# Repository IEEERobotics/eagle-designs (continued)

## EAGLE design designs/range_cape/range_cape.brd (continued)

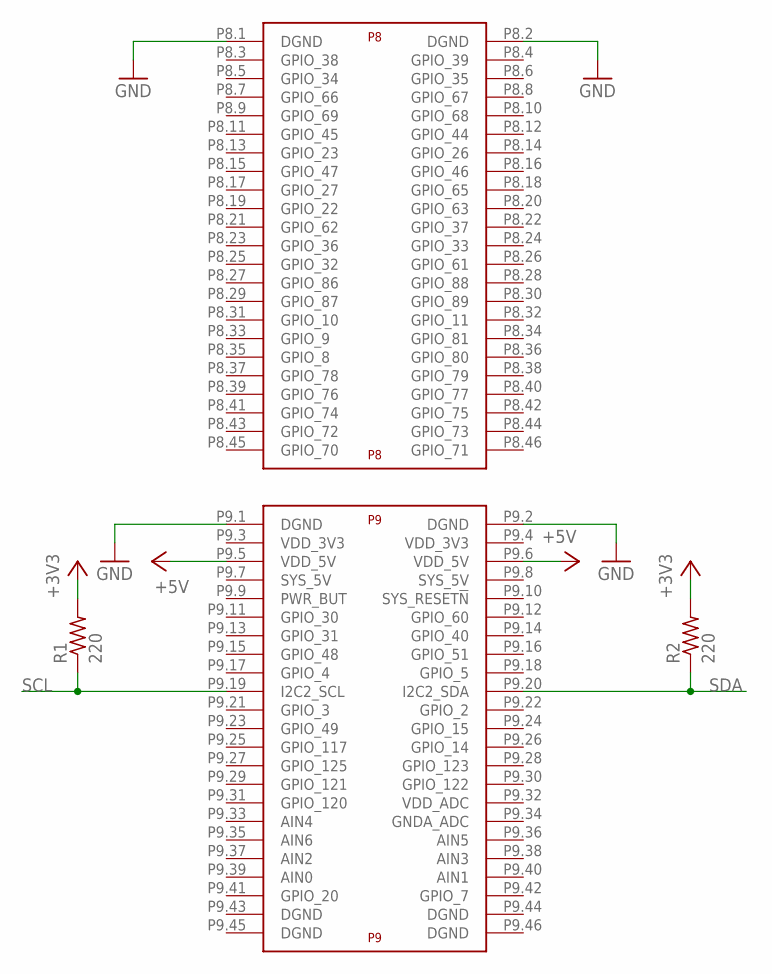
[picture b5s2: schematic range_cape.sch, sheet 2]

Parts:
R1, R2: 220; R0805W
U$1: BEAGLE_BONE_BLACK_CAPE

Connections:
+3V3: R1.2, R2.2; also elsewhere on the board
+5V: U$1.P9.5 (VDD_5V), U$1.P9.6 (VDD_5V); also elsewhere on the board
GND: U$1.P8.1 (DGND), U$1.P8.2 (DGND), U$1.P9.1 (DGND), U$1.P9.2 (DGND); also elsewhere on the board
SCL: R1.1, U$1.P9.19 (I2C2_SCL)
SDA: R2.1, U$1.P9.20 (I2C2_SDA)

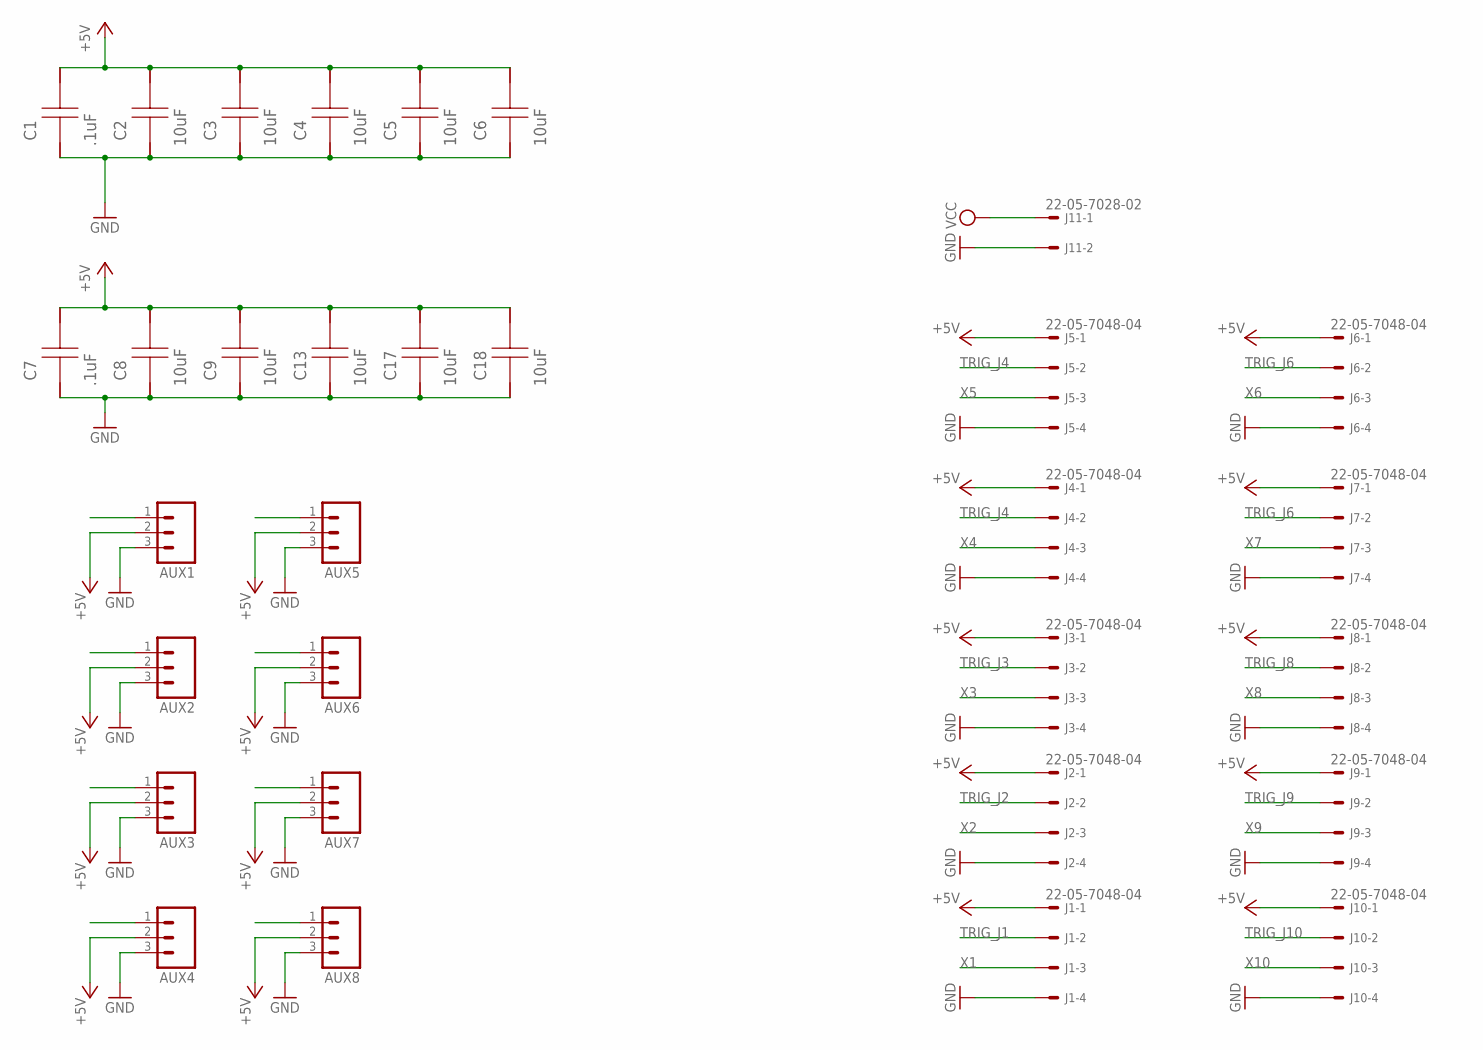
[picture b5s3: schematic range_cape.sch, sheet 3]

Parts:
AUX1, AUX2, AUX3, AUX4, AUX5, AUX6, AUX7, AUX8: M03LOCK; 1X03_LOCK
C1, C7: .1uF; 1206
C2, C3, C4, C5, C6, C8, C9, C13, C17, C18: 10uF; 1206
J1, J2, J3, J4, J5, J6, J7, J8, J9, J10: 22-05-7048-04; 7395-04
J11: 22-05-7028-02; 7395-02

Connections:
+5V: AUX1.2, AUX2.2, AUX3.2, AUX4.2, AUX5.2, AUX6.2, AUX7.2, AUX8.2, C1.1, C2.1, C3.1, C4.1, C5.1, C6.1, C7.1, C8.1, C9.1, C13.1, C17.1, C18.1, J1.1, J2.1, J3.1, J4.1, J5.1, J6.1, J7.1, J8.1, J9.1, J10.1; also elsewhere on the board
GND: AUX1.3, AUX2.3, AUX3.3, AUX4.3, AUX5.3, AUX6.3, AUX7.3, AUX8.3, C1.2, C2.2, C3.2, C4.2, C5.2, C6.2, C7.2, C8.2, C9.2, C13.2, C17.2, C18.2, J1.4, J2.4, J3.4, J4.4, J5.4, J6.4, J7.4, J8.4, J9.4, J10.4, J11.2; also elsewhere on the board
PWM_IN_1: AUX1.1; also elsewhere on the board
PWM_IN_2: AUX2.1; also elsewhere on the board
PWM_IN_3: AUX3.1; also elsewhere on the board
PWM_IN_4: AUX4.1; also elsewhere on the board
PWM_OUT_1: AUX5.1; also elsewhere on the board
PWM_OUT_2: AUX6.1; also elsewhere on the board
PWM_OUT_3: AUX7.1; also elsewhere on the board
PWM_OUT_4: AUX8.1; also elsewhere on the board
TRIG_J1: J1.2
TRIG_J2: J2.2
TRIG_J3: J3.2
TRIG_J4: J4.2, J5.2
TRIG_J6: J6.2, J7.2
TRIG_J8: J8.2
TRIG_J9: J9.2
TRIG_J10: J10.2
VCC: J11.1; also elsewhere on the board
X1: J1.3; also elsewhere on the board
X2: J2.3; also elsewhere on the board
X3: J3.3; also elsewhere on the board
X4: J4.3; also elsewhere on the board
X5: J5.3; also elsewhere on the board
X6: J6.3; also elsewhere on the board
X7: J7.3; also elsewhere on the board
X8: J8.3; also elsewhere on the board
X9: J9.3; also elsewhere on the board
X10: J10.3; also elsewhere on the board

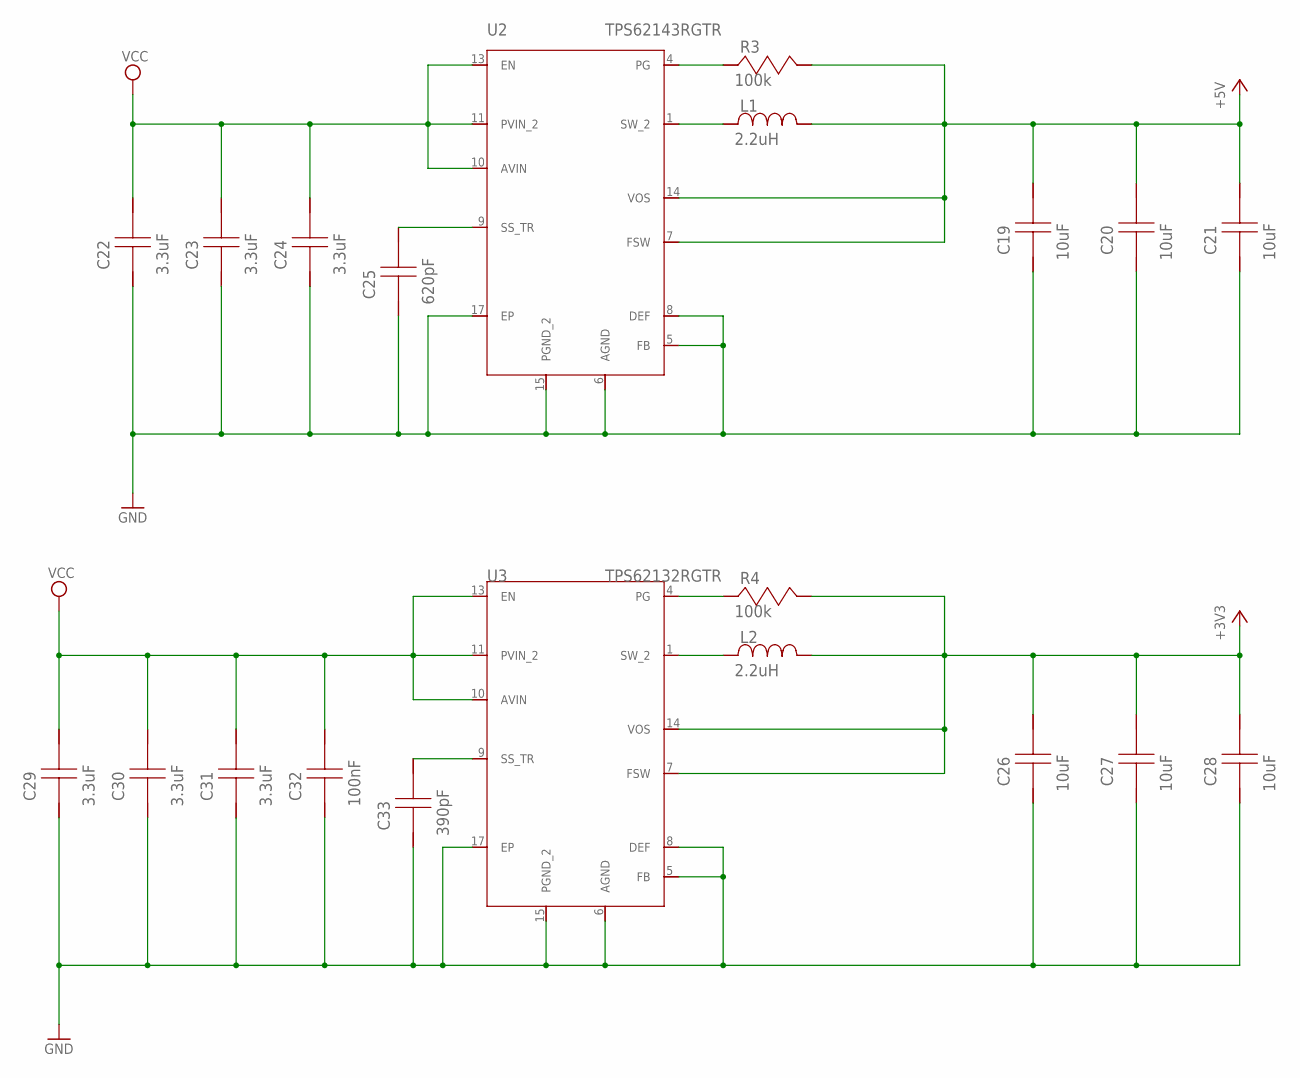
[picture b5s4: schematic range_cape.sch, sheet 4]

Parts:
C19, C20, C21, C26, C27, C28: 10uF; 1206
C22, C23, C24, C29, C30, C31: 3.3uF; C3216X7R1E335K
C25: 620pF; 0402
C32: 100nF; 0603
C33: 390pF; 0805
L1, L2: 2.2uH; IHLP-1212BZ
R3, R4: 100k; CRCW0402100KFKED
U2: TPS62143RGTR; S-PVQFN-N16
U3: TPS62132RGTR; S-PVQFN-N16

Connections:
+3V3: C26.1, C27.1, C28.1, L2.2, R4.1, U3.7 (FSW), U3.14 (VOS); also elsewhere on the board
+5V: C19.1, C20.1, C21.1, L1.2, R3.1, U2.7 (FSW), U2.14 (VOS); also elsewhere on the board
GND: C19.2, C20.2, C21.2, C22.2, C23.2, C24.2, C25.2, C26.2, C27.2, C28.2, C29.2, C30.2, C31.2, C32.2, C33.2, U2.5 (FB), U2.6 (AGND), U2.8 (DEF), U2.15 (PGND_2), U2.17 (EP), U3.5 (FB), U3.6 (AGND), U3.8 (DEF), U3.15 (PGND_2), U3.17 (EP); also elsewhere on the board
unnamed: L2.1, U3.1 (SW_2)
unnamed: L1.1, U2.1 (SW_2)
unnamed: C25.1, U2.9 (SS_TR)
unnamed: R3.2, U2.4 (PG)
unnamed: R4.2, U3.4 (PG)
unnamed: C33.1, U3.9 (SS_TR)
VCC: C22.1, C23.1, C24.1, C29.1, C30.1, C31.1, C32.1, U2.10 (AVIN), U2.11 (PVIN_2), U2.13 (EN), U3.10 (AVIN), U3.11 (PVIN_2), U3.13 (EN); also elsewhere on the board

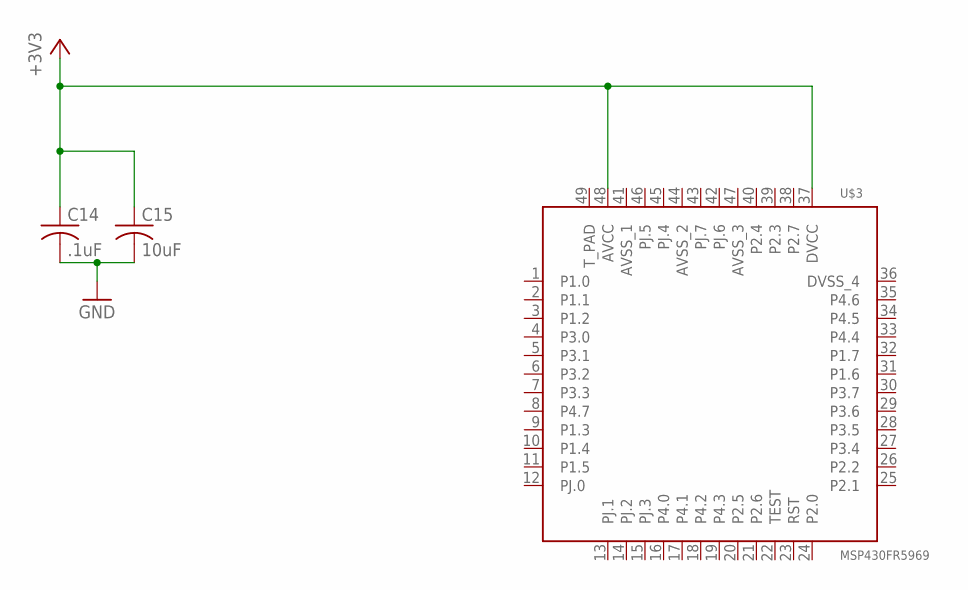
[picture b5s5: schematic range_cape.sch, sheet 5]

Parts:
C14: .1uF; C0805
C15: 10uF; C0805
U$3: MSP430FR5969; QFN50P700X700X100-49N

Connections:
DVCC: C14.1, C15.1, U$3.37 (DVCC), U$3.48 (AVCC)
GND: C14.2, C15.2; also elsewhere on the board

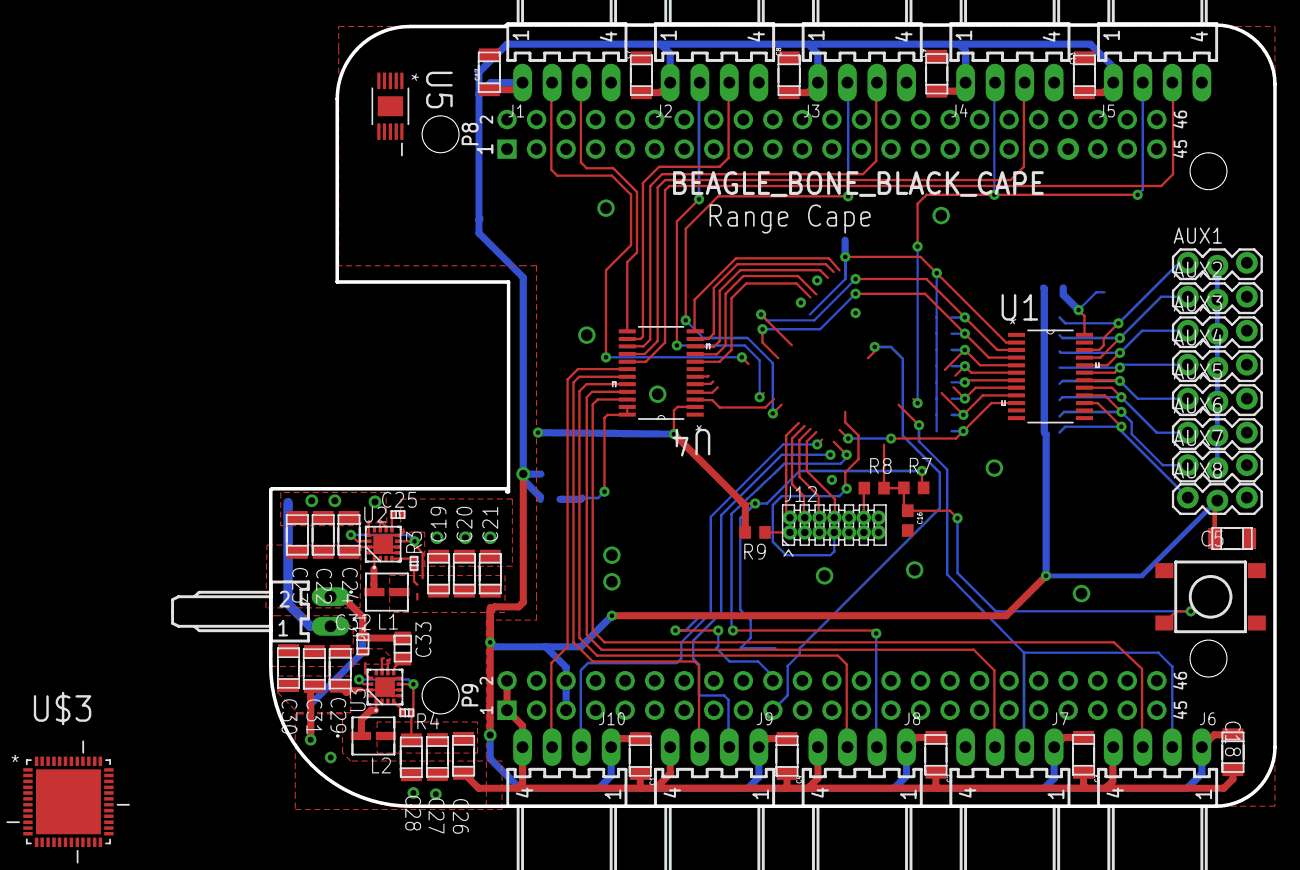
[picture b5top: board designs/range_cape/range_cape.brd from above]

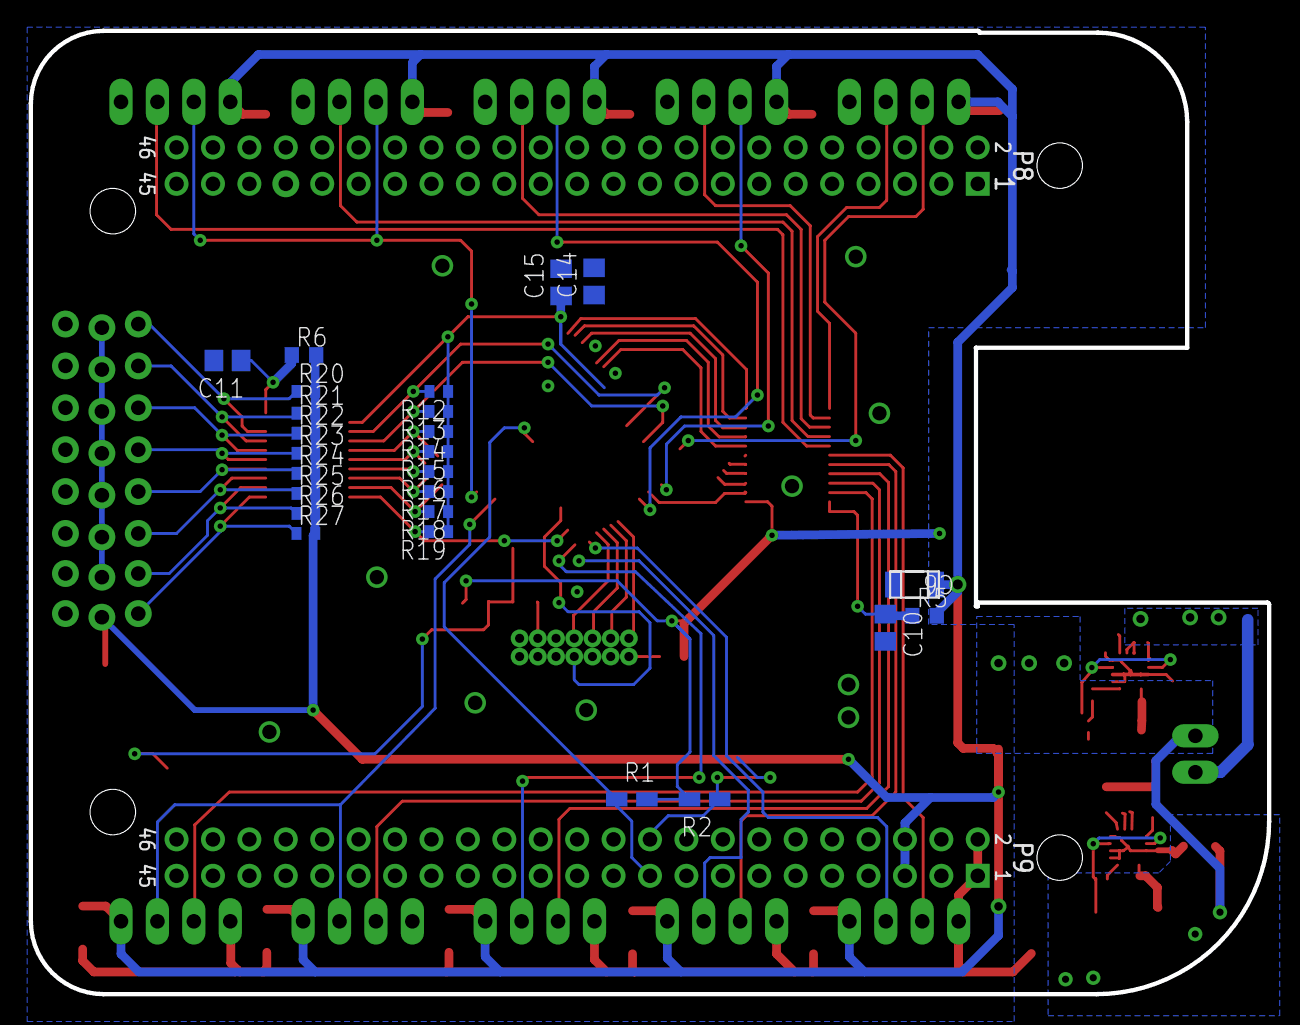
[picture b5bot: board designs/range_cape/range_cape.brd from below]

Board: 2 copper layers, 86.4 x 67.2 mm, 88 parts (25 on the bottom side), 46 nets.
